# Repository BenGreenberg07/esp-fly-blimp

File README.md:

# ESP-FLY Autonomous Blimp

Converting a tiny ESP32-S3 quadcopter into an **autonomous helium blimp** that flies
itself to motion-capture waypoints — hand-flyable and self-flying from a live browser
panel, commanded over a custom **ESP-NOW** radio link so the laptop never has to leave
the lab Wi-Fi.

This repo contains the full stack: the drone firmware, the USB↔radio bridge firmware,
the real-time 3D control/tuning panels, and the printable gondola.

```
OptiTrack ──Wi-Fi──▶ Laptop ──USB──▶ XIAO ESP32-C6 ──ESP-NOW──▶ ESP32-S3 (blimp)
 (pose stream)      (control panel)   (radio bridge)            (guidance + mixing)
```

The laptop stays on the mocap network the whole time — control rides a **separate
ESP-NOW radio path**, solving the "one Wi-Fi radio can't be on two networks at once"
problem.

---

# Getting started

## 1. Getting the code

Clone it or download it — either works. You only need the files on your computer — there is nothing to install
globally and no build step for the ground station.

```bash
git clone https://github.com/BenGreenberg07/esp-fly-blimp.git
cd esp-fly-blimp
```

No git? Click the green **Code ▾ → Download ZIP** button on GitHub and unzip it. Same
thing.

## 2. Minimum files required

**To FLY (ground station only) — this is most people, most of the time:**

| You need | Why |
|---|---|
| `run.py` | the launcher you press ▶ on |
| `config.json` | your Motive IP + rigid-body ID — **you must edit this** |
| `requirements.txt` | the three Python packages |
| `control/` | the panel server + the browser pages + the saved tuning |
| `optitrack_natnet/` | the mocap client (includes a macOS multicast fix) |

That's it. You can ignore `esp-drone/`, `espnow_bridge/`, `hardware/`, `docs/`, and
`archive/` entirely unless you are building or reflashing a blimp.

**To BUILD or REFLASH a blimp**, you also need `esp-drone/` (drone firmware),
`espnow_bridge/` (bridge firmware), and `hardware/` (the printable gondola). See
**[Building a blimp from scratch](#building-a-blimp-from-scratch)** below.

## 3. Install and configure

```bash
pip install -r requirements.txt
```

Then edit **`config.json`**:

```json
{ "motive_ip": "192.168.0.4", "body_id": 531, "up": "Z" }
```

| field | meaning |
|---|---|
| `motive_ip` | IP of the OptiTrack/Motive PC streaming NatNet |
| `body_id`   | the blimp's Rigid Body **Streaming ID** in Motive |
| `up`        | up axis, `"Z"` or `"Y"` (also togglable live in the panel) |

## 4. Run it

Open the folder in VS Code → **Run and Debug** (▶ in the left bar) → pick a panel and
press the green ▶. Or from a terminal:

```bash
python run.py --mode auto
```

The panel opens in your browser. Press **ARM** to connect the USB bridge, then fly.

> **Have running before you press ARM:** the blimp powered on, the ESP32-C6 bridge
> plugged into your computer, and your computer on the same network as the Motive PC.

**Nothing here needs a reflash.** Every gain is a live slider; the drone runs its own
guidance and the panel just streams pose, commands, and tuning to it.

## 5. What each script does

There are two scripts in this repo. The first is the one used for flying:

| Script | When you use it |
|---|---|
| **`run.py`** | **Every time you fly.** Starts the ground station: a small local web server plus the browser page you actually click on. |
| **`flash.py`** | **Rarely.** Only to put new firmware on a board. Not needed to fly, and not needed to change any gain. |

The word "panel" just means that browser page — the thing with the live 3D view, the
buttons, and the sliders. `--mode` picks which page you get (`auto`, `manual`, `wander`,
`swing`); they're all served by the same program.

**The controller is separate from the panel, and it isn't running on your laptop.** The
control math — steering toward the target, holding altitude — lives in the drone's own
firmware (`blimp_guidance.c`). Your laptop only tells it *where it is* and *where to go*,
and passes along gain changes when you move a slider. That's why nothing needs reflashing
when you tune, and why the path drawn on screen is a picture of what the drone is doing
rather than the thing steering it.

(The one exception is the experimental `swing` mode, where the controller does run on the
laptop — explained in [Next steps](#next-steps--the-s-blimp-4-motor-airframe).)

---

# Returning to a point after a hand push

Push the blimp by hand and it curves back to the point it was assigned. This needs no
special mode — it is a direct consequence of the constant-cruise pursuit controller.

1. `python run.py --mode auto`, then **ARM**.
2. Click **⋯ Path** (the path mode button in the *Auto path shape* card).
3. **Click once** in the 2D view, on the spot you want it to live. That single click is
   the whole configuration — one waypoint.
4. Leave **Loop** on. Press **▶ GO**.

It climbs to the target altitude, flies to your point, and then keeps circling it at its
minimum turn radius. Push it across the room and the steering carrot is still that one
point, so it banks around and comes back on a curve. Release it and it re-converges.

**It orbits rather than parks.** The forward motors run at constant cruise and can't
reverse, so the craft cannot brake to a stop — expect a slow circle around the point,
not a hover on it. If you want it to genuinely stop, sit still, and wait to be pushed,
use the **wander** panel instead (`python run.py --mode wander`): it cuts cruise on
arrival so the blimp coasts to a halt and is safe to grab, flashes the LED, waits for
your push, then flies to the next point.

### Suggested improvement: replace the constant cruise

The clearest place to take this further is the constant-cruise assumption itself. The
controller currently holds forward power fixed and only steers, which is what makes it
smooth on loops — but it is also the reason it can only orbit a point instead of settling
on it.

Worth building and testing: **a speed controller that modulates forward thrust by distance
to the target**, so the craft eases off as it approaches and coasts to a near-stop on the
point rather than circling it. Some useful starting material is already here:

- The **wander** mode already does a simple version — an approach taper that rolls cruise
  off linearly over the last metre or two, plus a `fwdMaxN = 0` "park" state on arrival.
  Generalising that into the main auto mode is the obvious first experiment.
- `control/flight_logs/plant_final_*.json` is an identified model of the vehicle's
  dynamics, so a stopping distance can be predicted rather than guessed. The craft coasts
  a long way: forward drag has a time constant of roughly 5–7 seconds.

Two things to expect. Because the motors cannot reverse, the approach has to be planned
early — by the time it is close, cutting thrust is the only remaining control. And below
roughly 0.15 m/s the constant sideways drift becomes comparable to the forward speed, so
creeping in slowly tracks *worse*, not better. A decelerating approach that still arrives
with some speed is likely the practical target. The complete fix is hardware: H-bridge
drivers giving the motors reverse thrust, and therefore actual braking — see
[Future additions](#future-additions).

---

# The four panels

All of them are the same server (`control/panel_server.py`) started in a different mode.
See **[control/README.md](control/README.md)** for the full detail.

### ⭐ Auto — `python run.py --mode auto` (port 8601)
The day-to-day tool. Streams your live mocap pose to the drone's **on-board guidance**
(firmware `blimp_guidance.c`) — pure-pursuit steering with a lookahead carrot plus an
altitude PID. Fly a drawn **path**, a **circle**, or a manual X/Y **point**.
Every gain is a live slider. Also has hand-fly, gamepad control, sys-ID test buttons, and
per-run CSV/PNG logging.

### Manual — `python run.py --mode manual` (port 8611)
Pure hand-fly, no autonomy: `W/S` forward, `A/D` turn, `Q/E` up/down, `Space` = kill,
plus hover-assist, trim, and per-direction power sliders. The simplest option for a first
flight, a bridge check, or a motor sanity check.

**Gamepad supported** (Auto mode has it too). An Xbox controller — or any USB/Bluetooth
pad the browser recognises — gives you *proportional* control instead of on/off keys:
**RT** = forward throttle, **right stick X** = turn, **left stick Y** = up/down,
**B** = KILL. The keyboard keeps working alongside it, and if the pad is unplugged or the
tab loses focus the panel falls back to the keys within a fraction of a second, so a
forgotten pad can never hold the motors on. Browsers only expose a gamepad after you
press a button on it, so "no pad" until first input is expected.

### Wander — `python run.py --mode wander` (port 8613)
Flies to a point (random within a box, or a list you click), **parks and coasts to a
stop**, flashes the drone LED to say "safe to touch", waits for a hand push, then picks
the next point. The push is detected from mocap speed, so no extra sensor.

### Swing — `python run.py --mode swing` (port 8620) — **untested**
The new 4-motor S-blimp airframe with an SE(3) Mellinger controller. Built and
bench-verified but **never flown**. See [Next steps](#next-steps--the-s-blimp-4-motor-airframe).

---

# Building a blimp from scratch

My custom build guide video: [https://youtu.be/fltrr_Snbas](url)

Start to finish, in the order you should actually do it.

### Step 1 — Parts

| Part | Notes |
|---|---|
| Seeed **XIAO ESP32-S3** micro-drone (ESP-Drone) | the flight board — 4 brushed motor channels |
| A second **XIAO ESP32-S3** (or ESP32-C6) | the USB↔ESP-NOW bridge that plugs into your laptop |
| 4× brushed coreless motors + props | 2 forward, 1 up, 1 down (see the mixer below) |
| Helium envelope (mylar) | must lift the gondola + battery with a little margin |
| 1S LiPo | small — weight is everything |
| Printed gondola | `hardware/` — see step 2 |
| OptiTrack / Motive + markers | for anything autonomous |

### Step 2 — Print the gondola

In **`hardware/`**:

| File | What it is |
|---|---|
| `gondola-frame-v5.stl` | the flying gondola — print this one |
| `balloon-mount-v2.stl` | the pad that tapes to the envelope |
| `s-blimp-frame-test2.stl` | the 4-motor S-blimp frame (next-gen, see below) |
| `blimp-gondola-mount.f3d`, `esp-blimp-frame.f3d` | Fusion 360 sources, if you want to change dimensions |

**Two geometry choices that matter more than any gain:**
- **Spread the two forward motors as wide as you can.** Yaw torque scales with their
  separation, and turn authority is the single biggest limit on this vehicle.
- **Mount the gondola centred under the envelope.** An off-centre mount gives a constant
  sideways drift that no controller can remove — this was measured and confirmed, and it
  is the dominant tracking error at low speed.

### Step 3 — Wire the motors

Motor roles are set in firmware, not by which wire you solder where, so you can fix a
mistake in software. The default map (`power_distribution_stock.c`):

```
M1 = DOWN      M2 = forward-LEFT      M3 = forward-RIGHT      M4 = UP
```

Verify it before you fly: `python control/check_link.py --spin` spins each channel
briefly at low power (**props off**) so you can see which motor is which. If they don't
match, edit the `MOTOR_FWD_LEFT / MOTOR_FWD_RIGHT / MOTOR_UP / MOTOR_DOWN` defines and
reflash — don't resolder.

### Step 4 — Flash the drone (ESP32-S3)

Install **ESP-IDF v5.0.x**, then:

```bash
cd esp-drone
idf.py set-target esp32s3      # FIRST TIME ONLY — the committed sdkconfig needs this
idf.py build
idf.py -p /dev/cu.usbmodemXXXX flash
```

Or let the helper script do all of that for you, on any OS:

```bash
python flash.py drone
```

It finds the port, sets up ESP-IDF if it isn't already on your PATH, and builds and
flashes in one step.

> **If flashing fails** with *"No serial data received"* or *"Invalid head of packet"*:
> the S3 talks over its internal USB-Serial-JTAG. Add `--before usb_reset`, or unplug the
> LiPo and replug the USB cable, then retry immediately. The chip is never damaged by a
> failed connect — esptool fails before it writes anything.

### Step 5 — Flash the bridge (ESP32-S3 or C6)

The bridge can be **either a XIAO ESP32-S3 or a XIAO ESP32-C6** — the same sketch builds
for both (the C6-only antenna switch is compiled out on an S3). An S3 is the easy choice
since it's the same board as the drone:

```bash
python flash.py bridge            # XIAO ESP32-S3 (default)
python flash.py bridge --board c6 # XIAO ESP32-C6
```

Needs `arduino-cli` with the Arduino **esp32 core 3.x**. The Arduino IDE works too — open
`espnow_bridge/espnow_bridge.ino` and pick board `XIAO_ESP32S3` or `XIAO_ESP32C6`.

> If you use `arduino-cli` by hand, note that `upload` on its own re-flashes the *last
> compiled* binary — always `compile --upload` together or you'll flash a stale sketch.
> (`flash.py` does this correctly for you.)

> **Using a C6?** Check whether your board has a u.FL external-antenna connector. The
> sketch enables the external antenna, so the physical antenna must be attached — with
> the switch set and no antenna fitted, range is *worse* than stock.

Your USB adapter will usually only show **one** port at a time, so flash the two boards
one after the other, not together.

### Step 6 — Bind the drone to its bridge

There is **no MAC address to type in**. Pairing is a 4-byte tag called `FRAME_MAGIC` that
both ends stamp on every packet and reject if it's missing — that's what stops your blimp
from being flown by the other ESP-NOW traffic in the room (which was a real bug: foreign
frames were being parsed as gain updates and crashing the drone).

A bridge and a drone are **bound when their `FRAME_MAGIC` values match**:

| File | Where |
|---|---|
| `espnow_bridge/espnow_bridge.ino` | search for `FRAME_MAGIC` (~line 42) |
| `esp-drone/components/espnow_control/espnow_control.c` | search for `FRAME_MAGIC` (~line 46) |

Out of the box both are `{0xB1, 0x12, 0x9F, 0x5A}` and one drone works with no changes.

**Flying a second blimp in the same room:** give triplet #2 (its own laptop + bridge +
drone) a different `FRAME_MAGIC` — any 4 bytes — set **identically in both files**, then
reflash **both** of its boards. Leave triplet #1 and `TELEM_MAGIC` alone, and keep
everyone on channel 1. Full write-up: [espnow_bridge/README.md](espnow_bridge/README.md).

### Step 7 — First flight

1. Fill the envelope so it is **very slightly negatively buoyant** — it should sink
   slowly when you let go. Trim with tape.
2. Plug the C6 into the laptop, power the blimp.
3. `python control/check_link.py` — confirms the drone is actually replying over
   ESP-NOW (motor telemetry, not just an open serial port). Do this before blaming the
   panel.
4. `python run.py --mode manual` → **ARM** → hand-fly it. Get up/down and turning
   working, and set the power sliders where it feels controllable.
5. Only then go autonomous: `python run.py --mode auto`, create your rigid body in
   Motive, check the tracking pill goes green, and try the
   [come-back-when-pushed](#make-it-come-back-when-you-push-it) recipe above.

**If it turns the wrong way**, hit **⟳ Flip turn direction** in the panel (it flips the
sign of `turnMaxPwm`). Don't rewire.

---

# Tuning

Every gain — manual powers/trims and autonomous pursuit/hover gains — is a live slider.
Values ride the ESP-NOW link and update the controller in RAM instantly, with no reflash.
The panels are **self-contained** (pure-canvas 2D/3D, no CDNs) so they run on a
locked-down lab network, and they save automatically.

`control/mocap_config.json` ships with **the tuning currently flying on my blimp**, so a
fresh clone starts from known-good numbers instead of defaults:

| | |
|---|---|
| `fwdMaxN` 0.18 | constant forward cruise — the main speed/turn-radius trade |
| `kpHead` 2.65, `kdHead` 0.037 | pursuit steering PD (kd is the anti-overshoot term) |
| `turnCap` 0.9, `turnBoost` 0.35 | turn authority and how symmetric the differential is |
| `driftK` 1.3 | crab into the sideways drift |
| `zff` 19000, `vertMaxPwm` 28000 | buoyancy feedforward and its output ceiling |

**Radius scales with speed.** Flying wider circles than you drew is almost always
`fwdMaxN` being too high, not a steering gain. Slowing down is the strongest lever.

# Repo layout

```
run.py                  ▶ the launcher (VS Code ▶, or `python run.py --mode auto`)
config.json             your Motive IP + rigid-body IDs — EDIT THIS
requirements.txt        Python deps (numpy, matplotlib, pyserial)

control/                the ground station — everything you need to fly
  ├─ panel_server.py          the server behind all four modes
  ├─ auto_panel.html          Auto page (2D/3D mocap view, path drawing, live tuning)
  ├─ manual_panel.html        Manual hand-fly page
  ├─ wander_panel.html        Wander page (park → wait for a push → next point)
  ├─ swing_panel.html         Swing / S-blimp page (untested)
  ├─ swing_panel_server.py    Swing server — separate controller and motor layout
  ├─ mellinger_core.py        SE(3) Mellinger controller + the geometry-driven mixer
  ├─ swing_trajectory.py      trajectory generator for the swing build
  ├─ mocap_config.json        the tuning that is currently flying
  ├─ check_link.py            terminal-only link + motor test (run this first)
  └─ flight_logs/plant_final_*.json    identified dynamics model

hardware/               printable gondola (STL) + Fusion 360 sources + the S-blimp photo
esp-drone/              on-board drone firmware (ESP-IDF, ESP-Drone derivative)
espnow_bridge/          XIAO ESP32-C6 USB↔ESP-NOW bridge (Arduino) + pairing guide
optitrack_natnet/       OptiTrack NatNet client (incl. a macOS multicast fix)
docs/                   design notes and write-ups
archive/                earlier / superseded tools kept for history
```

Inherited the physical hardware rather than building your own? The specific IDs,
addresses, and quirks of the blimp I actually flew are in
[docs/THIS_EXACT_BLIMP.md](docs/THIS_EXACT_BLIMP.md).

### On-board firmware (custom components)
Built on Espressif's [ESP-Drone](https://github.com/espressif/esp-drone) (a Crazyflie
port). The custom work:
- `.../blimp_guidance.c` — the on-board guidance controller (pursuit + carrot + altitude
  PID + soft-start + spin abort)
- `.../power_distribution_stock.c` — blimp motor mixer (constant-forward + differential
  turn, vertical sign/dead-band) and the swing-build 4-motor branch
- `.../stabilizer.c`, `.../system.c` — blimp flight mode + radio-link selection
- `components/espnow_control/` — ESP-NOW receiver (manual + pose + gains frames, magic-tag
  filtering, link-loss failsafe) and the motor-telemetry return path
- `components/ble_control/` — BLE control link (parked)

---

# Next steps — the S-blimp 4-motor airframe

The next airframe replaces "2 forward + 1 up + 1 down" with **four motors on an X-frame,
all pointing roughly upward, canted about 45°** (photo above; frame is
`hardware/s-blimp-frame-test2.stl`).

**Motivation.** The current blimp's problems all trace back to one thing: the only
horizontal actuator is a pair of unidirectional forward motors, so it can't brake, can't
rotate in place, and drifts sideways through every turn. Four canted motors change the
actuation entirely — vertical thrust and yaw come out directly, and horizontal motion
comes from **tilting the envelope so the gondola's pendulum swings and the tilted lift
vector pulls it along** (hence "swing blimp").

**What already exists in this repo (built, bench-tested, `--mode swing`):**
- `control/mellinger_core.py` — a port of the Bitcraze **SE(3) Mellinger** controller,
  running host-side because it needs the full attitude quaternion every tick and the
  pose frame only carries position + yaw.
- A **geometry-driven mixer**: per-motor position + thrust axis → a 4×4 allocation
  matrix, solved by damped least-squares because the matrix is **singular by design**.
  Three switchable cant layouts (`lateral`, `foreaft`, `tangential`); unachievable force
  is routed into a moment, which is what makes the swing happen.
- Firmware support behind `#define BLIMP_SWING` (default 0 — nothing changes until you
  set it). In this build the drone is a **dumb 4-channel motor amplifier** and the wire
  format is the unchanged `0xA5` frame, so **only the drone reflashes, not the bridge**.
- A panel with props-off per-motor bench buttons and a motor-map editor, so you map
  channels to arms by clicking rather than resoldering.

**Remaining work:**
1. `python flash.py swing` (drone only; `python flash.py drone` puts the old blimp back).
2. Props off — bench-test M1..M4 and set the motor map from what actually spins.
3. Confirm the real cant matches a layout — watch which allocation row reads zero.
4. Raise `hover` until it floats, then ENGAGE with the target at its current position.
5. **Start the rate-D gains (`kw_*`, `kd_omega_rp`) well below the reference values** —
   they assume a 500 Hz IMU, but here body rates come from 25 Hz mocap.

---

# Future additions

### PCB with an integrated ESP32
Today the flight board is a XIAO module soldered onto a carrier — the between-board
joints are the most fragile thing on the vehicle and they add height and weight. The plan
is a **custom PCB with the ESP32-S3 native on the board**: no module, no inter-chip
soldering, one part to place.

### H-bridge motor drivers for reverse thrust
The single biggest limitation of the whole design is that the brushed motors are driven
by one low-side MOSFET each, so they only spin one way. Adding **H-bridge drivers
(e.g. DRV8833)** would let the forward motors reverse, which buys:
- **turning in place** — oppose the two forward motors instead of arcing
- **braking**, so it can actually stop on a point instead of orbiting it
- much tighter path tracking, since the min-turn-radius floor largely goes away

This needs signed PWM in the mixer and a firmware reflash once the hardware is wired.

**PCB design files and work-in-progress:**
[Google Drive folder](https://drive.google.com/drive/folders/18QSSe5u8A_p2iix2rqLfaRU-QODWJp0w)

---

# Wi-Fi mode (fallback, and how to revert)

ESP-NOW is the primary control link, but the drone **also brings up its own Wi-Fi access
point**, so Wi-Fi control is available at any time with no reflashing.

| Setting | Value |
|---|---|
| SSID | `ESP-DRONE_xxxxxxxxxxxx` |
| Password | `12345678` |
| Control link (CRTP over UDP) | `udp://192.168.43.42:2390` |

There's no bundled panel for this path — drive it with `cflib`'s `cfclient` or your own
script. Older keyboard-teleop clients (`drive_blimp*.py`) are in `archive/`.

**To make Wi-Fi the *only* radio**, edit
`esp-drone/components/core/crazyflie/modules/src/system.c`:

```c
#define ESPNOW_CONTROL_ENABLED 0   // 1 = ESP-NOW (default), 0 = Wi-Fi only
#define BLE_CONTROL_ENABLED    0   // (BLE link, normally off)
```

then rebuild and flash.

---

# Troubleshooting

**If the panel will not connect, or nothing moves,** run the terminal-only check first — it opens
the bridge, confirms the drone is really replying over ESP-NOW, and can spin each motor:

```bash
python control/check_link.py                       # test the link only (no spin)
python control/check_link.py --spin                # + spin each channel briefly, props OFF
python control/check_link.py --bridge-port COM5    # if auto-detect picks the wrong port
```

| Symptom | Cause |
|---|---|
| Tracking pill never goes green | laptop isn't on the mocap network, or the wrong `body_id` |
| Flies wider circles than drawn | `fwdMaxN` too high — slow it down |
| Turns the wrong way | **⟳ Flip turn direction** in the panel |
| Sinks during flight | buoyancy or battery sag, not gains — check `zff` isn't above `vertMaxPwm` |
| Random jitter / drone reboots ~3 s in | another ESP-NOW device in the room; check `FRAME_MAGIC` matches on both your boards |

---

# License
The `esp-drone/` firmware is a derivative of Espressif ESP-Drone and remains **GPL-3.0**
(original license headers retained). The host-side tools, panels, and hardware are
original work by the author.

---

*Built by Ben Greenberg. An exercise in re-purposing a flight controller, control design
around a hard actuation constraint, embedded radio links, and real-time tooling.*

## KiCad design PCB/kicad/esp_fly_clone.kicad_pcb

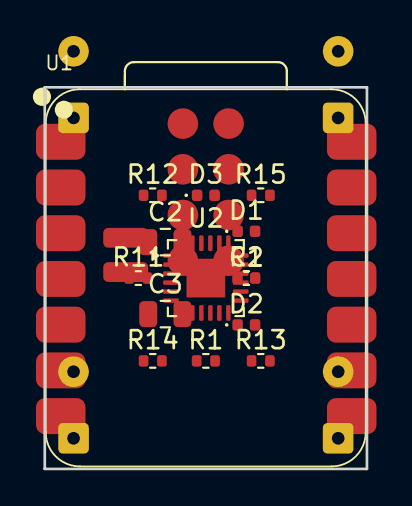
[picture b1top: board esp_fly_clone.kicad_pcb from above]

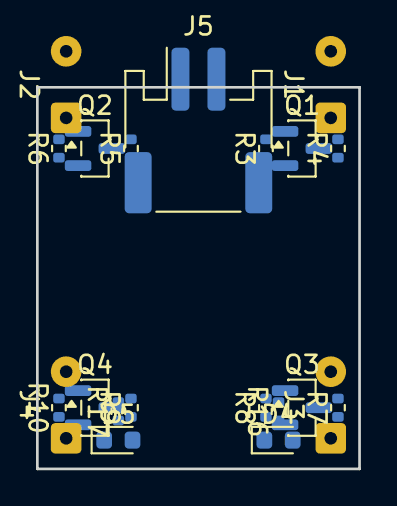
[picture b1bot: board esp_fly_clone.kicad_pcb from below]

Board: 4 copper layers, 17.9 x 21.2 mm, 36 parts (21 on the bottom side), 27 nets, no tracks yet.

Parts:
C1: 100n; C_0402_1005Metric
C2, C3: 22u; C_0805_2012Metric
D1: R; LED_0402_1005Metric
D2: G; LED_0402_1005Metric
D3: B; LED_0402_1005Metric
D4, D5: white; LED_0603_1608Metric
J1: Motor1; SolderWire-0.127sqmm_1x02_P3.7mm_D0.48mm_OD1mm
J2: Motor2; SolderWire-0.127sqmm_1x02_P3.7mm_D0.48mm_OD1mm
J3: Motor3; SolderWire-0.127sqmm_1x02_P3.7mm_D0.48mm_OD1mm
J4: Motor4; SolderWire-0.127sqmm_1x02_P3.7mm_D0.48mm_OD1mm
J5: JST-PH 1S; JST_PH_S2B-PH-SM4-TB_1x02-1MP_P2.00mm_Horizontal
Q1, Q2, Q3, Q4: SI2302; SOT-23
R1, R2, R4, R6, R8, R10: 10k; R_0402_1005Metric
R3, R5, R7, R9: 100; R_0402_1005Metric
R11, R12: 100k; R_0402_1005Metric
R13, R14, R15, R16, R17: 150; R_0402_1005Metric
U1: XIAO_ESP32S3; XIAO-ESP32S3-SMD
U2: MPU-6050; QFN-24-1EP_4x4mm_P0.5mm_EP2.15x2.15mm

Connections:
+3V3: C1.1, R1.1, R2.1, R13.1, R14.1, R15.1, R16.1, R17.1, U1.12, U2.8, U2.13
GND: C1.2, C2.2, C3.2, D4.1, D5.1, J5.2, Q1.2, Q2.2, Q3.2, Q4.2, R4.2, R6.2, R8.2, R10.2, R12.2, U1.13, U1.16, U1.20, U2.9, U2.18
I2C_SCL: R2.2, U1.6, U2.23
I2C_SDA: R1.2, U1.5, U2.24
LED_B: D3.1, U1.8
LED_G: D2.1, U1.7
LED_R: D1.1, U1.11
MOT1: R3.1, U1.1
MOT2: R5.1, U1.2
MOT3: R7.1, U1.3
MOT4: R9.1, U1.4
MPU_INT: U1.9, U2.12
unnamed: Q1.1, R3.2, R4.1
unnamed: J1.2, Q1.3
unnamed: Q2.1, R5.2, R6.1
unnamed: J2.2, Q2.3
unnamed: Q3.1, R7.2, R8.1
unnamed: J3.2, Q3.3
unnamed: Q4.1, R9.2, R10.1
unnamed: J4.2, Q4.3
unnamed: D1.2, R13.2
unnamed: D2.2, R14.2
unnamed: D3.2, R15.2
unnamed: D4.2, R16.2
unnamed: D5.2, R17.2
VBAT: C2.1, C3.1, J1.1, J2.1, J3.1, J4.1, J5.1, R11.1, U1.15
VBAT_SENSE: R11.2, R12.1, U1.10

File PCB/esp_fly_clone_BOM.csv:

Comment,Designator,Footprint,LCSC Part #,Notes
SI2302 N-MOSFET,"Q1,Q2,Q3,Q4",SOT-23,C10487,motor low-side drivers
MPU-6050,U2,QFN-24-4x4,C24112,IMU (I2C addr 0x68)
22uF 10V,"C1,C2",C_0805,C45783,VBAT bulk
100nF,C3,C_0402,C1525,IMU decoupling
10k,"R1,R2",R_0402,C25744,I2C SDA/SCL pullups
10k,"R3,R4,R5,R6",R_0402,C25744,MOSFET gate pulldowns
100R,"R7,R8,R9,R10",R_0402,C25076,MOSFET gate series
100k,"R11,R12",R_0402,C25741,battery sense divider
150R,"R13,R14,R15,R16,R17",R_0402,C25092,LED series resistors
LED red,D1,LED_0402,,status
LED green,D2,LED_0402,,status
LED blue,D3,LED_0402,,status
LED white,"D4,D5",LED_0603,,power indicators
JST-PH 2.0 2P,J5,JST_PH_S2B,C173752,1S battery
XIAO ESP32-S3,U1,XIAO-ESP32S3-SMD,,DNP - user solders module on top
Motor pads,"J1,J2,J3,J4",SolderWirePad_1x02,,motors hand-soldered

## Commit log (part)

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2026-06-26 ESP-FLY autonomous blimp: on-board decoupled PID, ESP-NOW bridge, mocap 3D control panel
2026-06-26 Include NatNet client files (was an embedded repo)
2026-06-26 docs: add Wi-Fi mode (fallback + how to revert) section to README
2026-06-26 Cascade rate-limited yaw controller + forward-only tune preset
    Heading loop is now a heading->yaw-rate cascade (capped turn rate) so a large
    low-damping envelope can't wind up into an unrecoverable spin. Gains frame grows
    to 15 floats; panel adds live cascade sliders + a forward-only tuning preset.
2026-06-30 Forward velocity damping (anti-overshoot), persistent tuning, sign/axis fixes
    - kdFwd: drone finite-diffs mocap pose -> eases off forward thrust early so it
    coasts to the target instead of overshooting (motors can't reverse-brake)
    - panel tuning now persists to mocap_config.json across reboots
    - yaw + vertical sign corrections, display X flip, X/Y/Z trend plots
